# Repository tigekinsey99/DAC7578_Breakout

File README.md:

# DAC7578_Breakout
This is a breakout board for the Texas Instruments [DAC7578](https://www.ti.com/product/DAC7578). An mbed driver is also included along with a [link](https://www.digikey.com/short/53d7nqw4) containing all the components needed to assemble the board.

## Motivation
The Mbed only supports one analog output pin. We wanted the user to have more analog outputs. The DAC7578 is a 12-bit 8 channel DAC that interfaces via I2C. This gives the user 8 more analog outputs with 12 bits of precision with the sacrifice of an I2C address, 2 pins for SDA and SCL and potentially a few more pins if the user wishes to use the DAC7578's additional functionalities.

## 12-bit, Octal Channel, Ultra-Low Glitch, Voltage Output, 2-Wire Interface DAC DAC7578
The DAC7578 is a low-power, voltage-output, octal–channel, digital-to-analog converter (DAC). The device is monolithic, provides good linearity, and minimizes undesired code-to-code transient voltages (glitch).

## Notes
THE DAC7578 offers 12-bits of resolution when outputing a voltage ranging from 0 to AVDD. Power consumption is typically 2.32 mW at 3V, reducing to 0.68uW in power-down mode.

## DAC7578 Key Features
* 12 bit: 1LSB INL
* Power-On Reset to Zero Scale or Midscale
* Ultra-Low Power Operation: 0.13mA/ch at 5V
* Wide Power-Supply Range: +2.7V to +5.5V
* 2-Wire Serial Interface (I2C compatible)
* Temperature Range: -40C to +125C

## Additional Functionalities
The DAC7578 has an active low LDAC pin that allows the user to update user selected DAC channel registers asynchronously through the falling edge of the LDAC control signal. To use the DAC7578 in synchronous mode, keep LDAC tied low.

The DAC7578 also has an active low NCLR pin to clear the data stored in all the DAC channel registers to either zero scale, mid scale, or full scale voltages depending on the data stored in the clear code register. A clear activates on the falling edge of the NCLR pin.

## DAC7578 and Breakout Pinout

## Datasheet
[DAC7578 Datasheet](https://www.ti.com/lit/ds/symlink/dac7578.pdf?ts=1670937258903&ref_url=https%253A%252F%252Fgoogle.com)

## Block Diagram

## Schematic

## 3D Photo

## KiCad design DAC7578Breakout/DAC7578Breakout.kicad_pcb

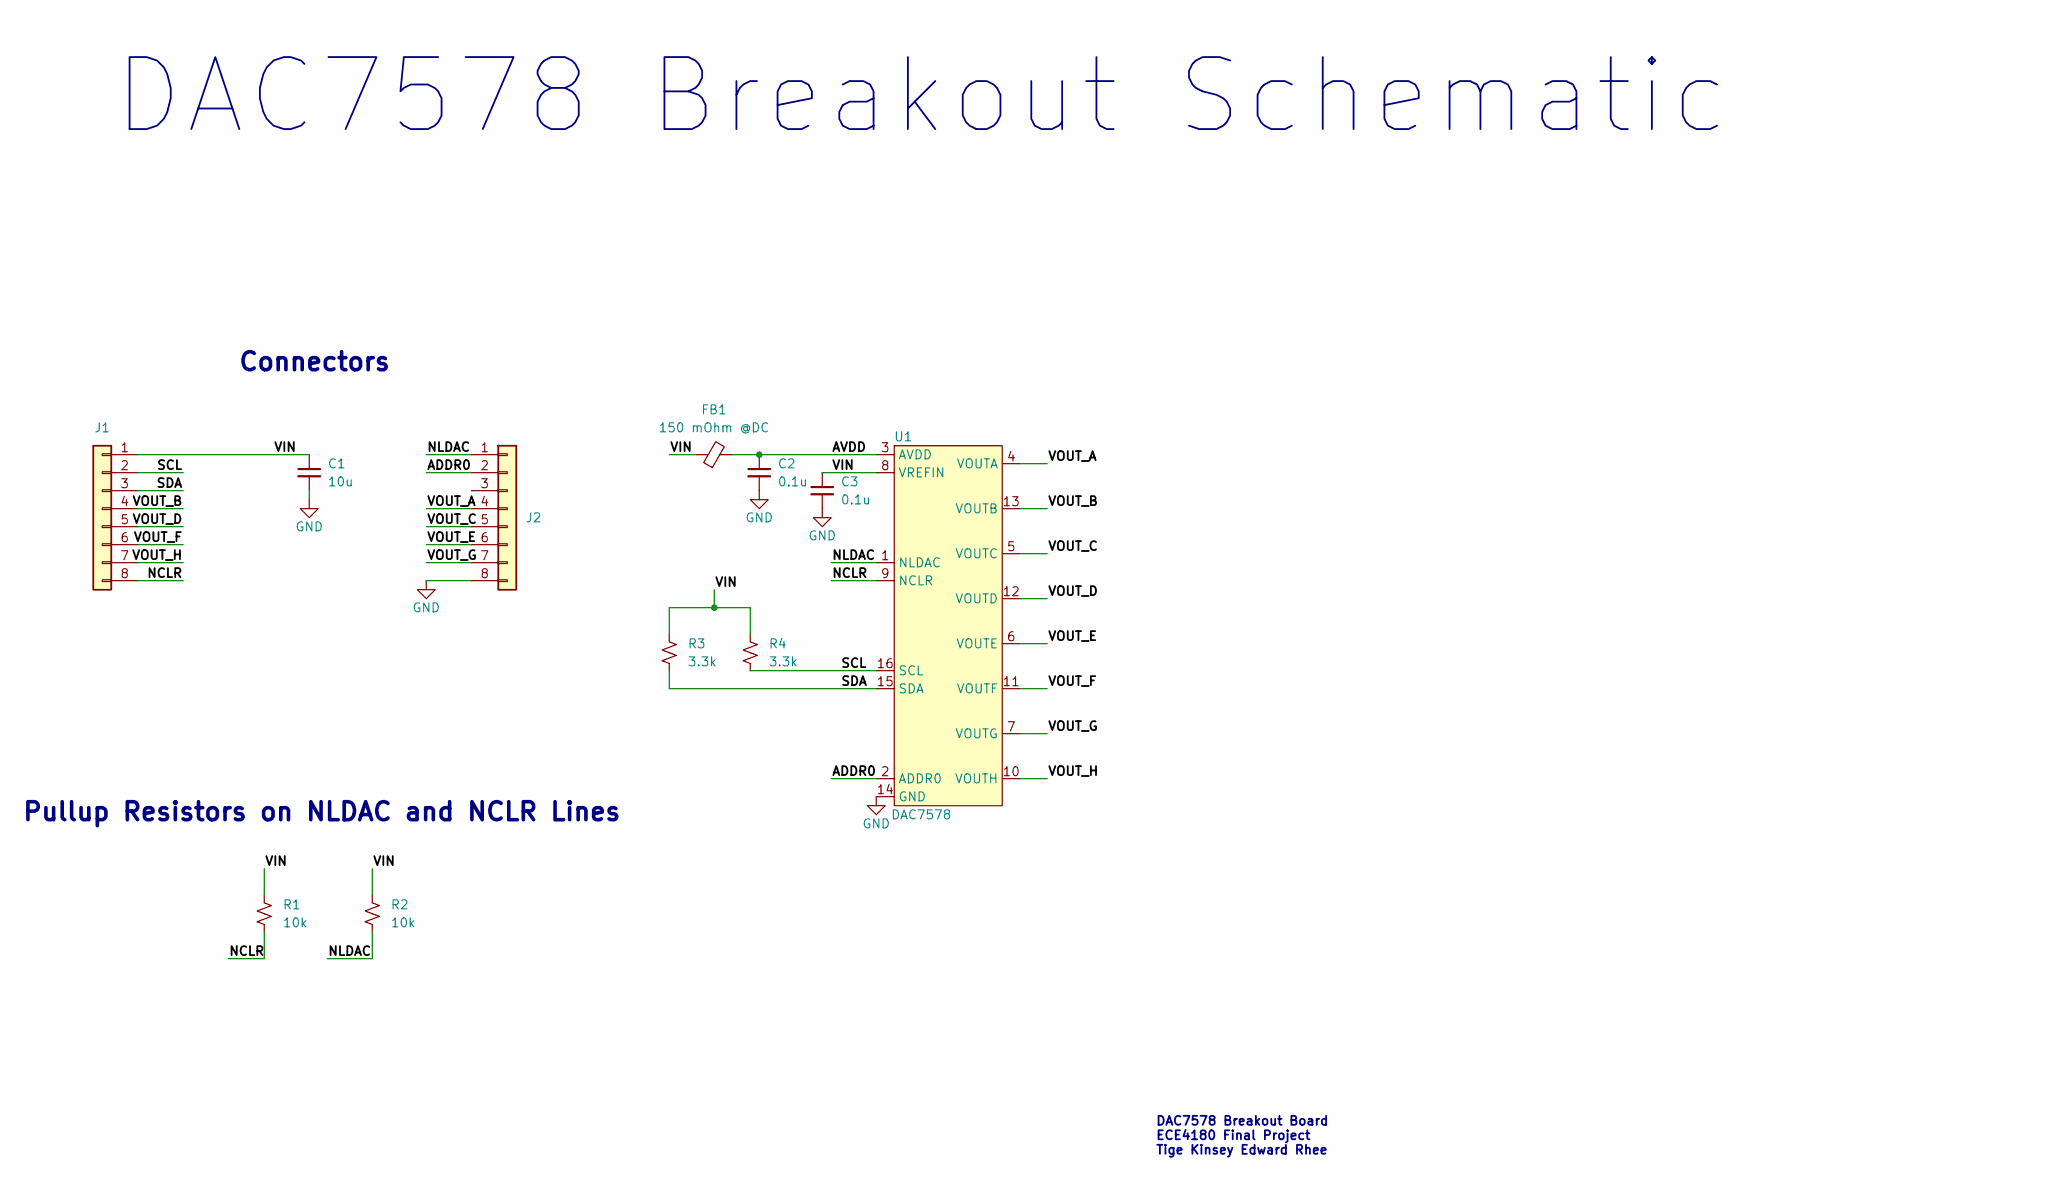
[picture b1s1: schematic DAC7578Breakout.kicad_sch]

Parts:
C1: 10u; C_0603_1608Metric_Pad1.08x0.95mm_HandSolder
C2, C3: 0.1u; C_0603_1608Metric_Pad1.08x0.95mm_HandSolder
FB1: 150 mOhm @DC; R_0603_1608Metric_Pad0.98x0.95mm_HandSolder
J1, J2: Conn_01x08; PinHeader_1x08_P2.54mm_Vertical
R1, R2: 10k; R_0805_2012Metric_Pad1.20x1.40mm_HandSolder
R3, R4: 3.3k; R_0805_2012Metric_Pad1.20x1.40mm_HandSolder
U1: DAC7578

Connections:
/ADDR0: J2.2, U1.2 (ADDR0)
/AVDD: C2.1, FB1.2, U1.3 (AVDD)
/NCLR: J1.8, R1.2, U1.9 (NCLR)
/NLDAC: J2.1, R2.2, U1.1 (NLDAC)
/SCL: J1.2, R4.2, U1.16 (SCL)
/SDA: J1.3, R3.2, U1.15 (SDA)
/VIN: C1.1, C3.1, FB1.1, J1.1, R1.1, R2.1, R3.1, R4.1, U1.8 (VREFIN)
/VOUT_A: J2.4, U1.4 (VOUTA)
/VOUT_B: J1.4, U1.13 (VOUTB)
/VOUT_C: J2.5, U1.5 (VOUTC)
/VOUT_D: J1.5, U1.12 (VOUTD)
/VOUT_E: J2.6, U1.6 (VOUTE)
/VOUT_F: J1.6, U1.11 (VOUTF)
/VOUT_G: J2.7, U1.7 (VOUTG)
/VOUT_H: J1.7, U1.10 (VOUTH)
GND: C1.2, C2.2, C3.2, J2.8, U1.14 (GND)

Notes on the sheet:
Pullup Resistors on NLDAC and NCLR Lines
Connectors
DAC7578 Breakout Board ECE4180 Final Project Tige Kinsey Edward Rhee
DAC7578 Breakout Schematic

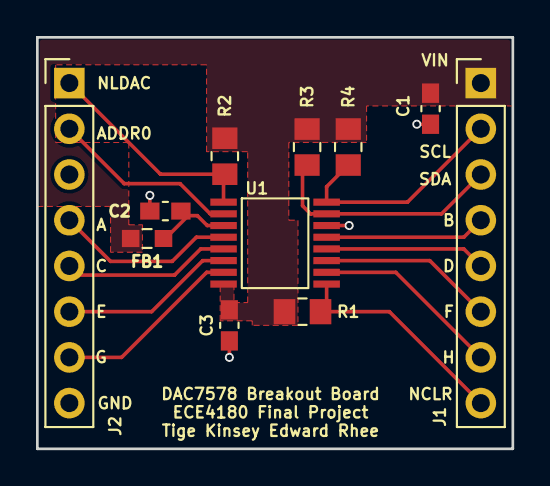
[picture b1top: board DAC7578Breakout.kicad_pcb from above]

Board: 2 copper layers, 26.4 x 22.9 mm, 11 parts (0 on the bottom side), 16 nets.

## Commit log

2022-11-22 schematic and pcb
2022-11-26 Finish pcb
2022-12-01 pcb files
2022-12-01 mbed
2022-12-01 mbed code
2022-12-12 add write and update functions
2022-12-13 Readme and silkscreen
2022-12-13 gerber and readme
2022-12-13 readme
2022-12-13 demo code
